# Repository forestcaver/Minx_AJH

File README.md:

# Minx_AJH

Buffered multiple based on Mutable Instruments Links

v1.1 normals the first input jack to ground (if you have v1.0 boards - it's trivial to just jumper the jack !)

BOM spreadsheet is untested - I havent built from this BOM ! Pls check carefully if you use it.

Please note - pcbs and panels are being sold by other people - I have no connection, financial or otherwise, to anyone selling pcbs and panels, hence I feel no commercial obligation to offer build support! I am just freely offering up these designs! Enjoy!

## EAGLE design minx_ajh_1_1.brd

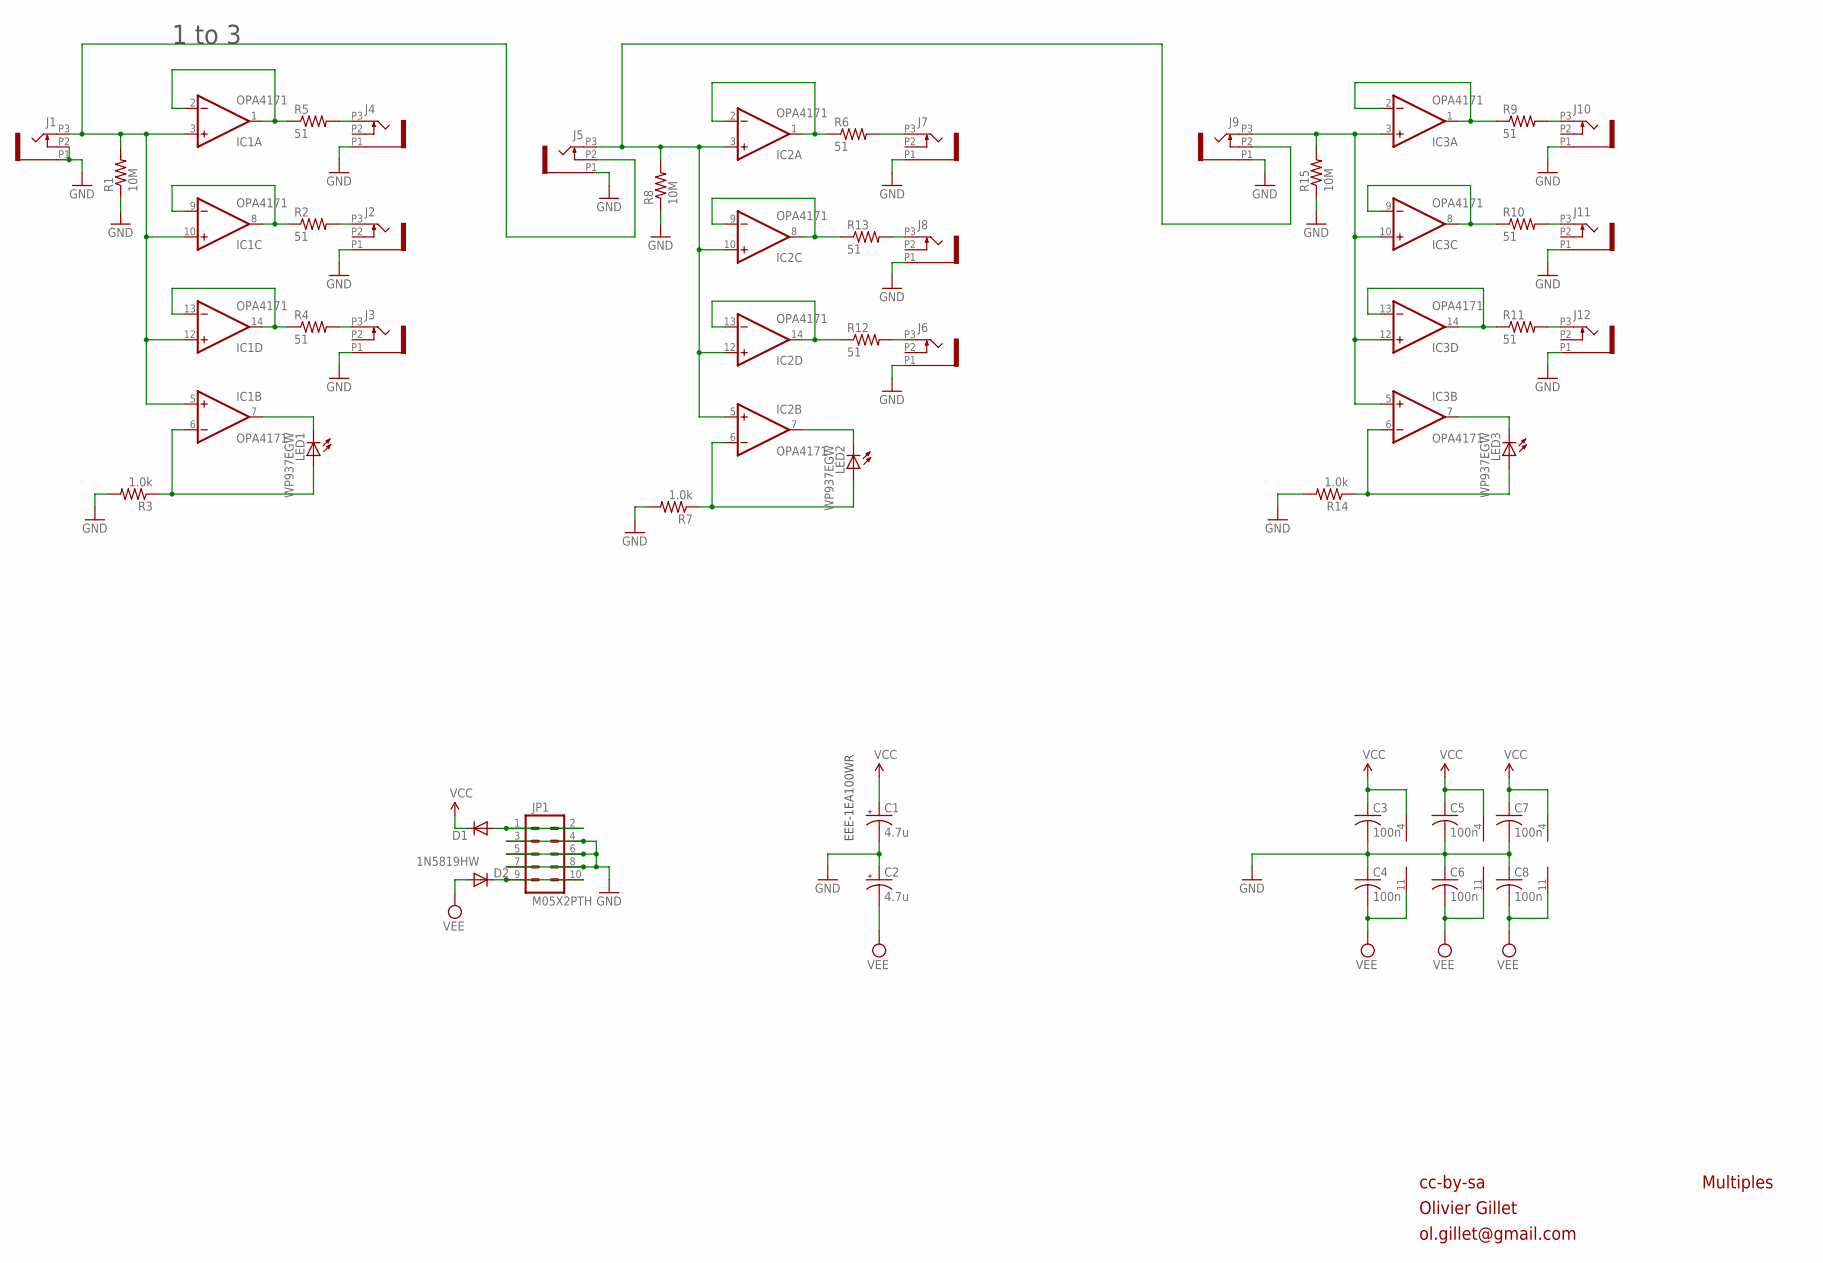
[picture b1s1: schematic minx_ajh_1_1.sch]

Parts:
C1, C2: 4.7u; PANASONIC_A
C3, C4, C5, C6, C7, C8: 100n; C0603
D1, D2: 1N5819HW; SOD123
IC1, IC2, IC3: OPA4171; TSSOP14
J1, J2, J3, J4, J5, J6, J7, J8, J9, J10, J11, J12: PJ301_THONKICONN6; WQP_PJ_301M6
JP1: M05X2PTH; AVR_ICSP
LED1, LED2, LED3: WP937EGW; LED3MM
R1, R8, R15: 10M; R0603
R2, R4, R5, R6, R9, R10, R11, R12, R13: 51; R0603
R3, R7, R14: 1.0k; R0603

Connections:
GND: C1.-, C2.+, C3.2, C4.1, C5.2, C6.1, C7.2, C8.1, J1.P1 (1), J1.P2 (2), J2.P1 (1), J3.P1 (1), J4.P1 (1), J5.P1 (1), J6.P1 (1), J7.P1 (1), J8.P1 (1), J9.P1 (1), J10.P1 (1), J11.P1 (1), J12.P1 (1), JP1.3, JP1.4, JP1.5, JP1.6, JP1.7, JP1.8, R1.1, R3.2, R7.2, R8.1, R14.2, R15.1
unnamed: IC2.8 (OUT), IC2.9 (-IN), R13.1
unnamed: IC3.1 (OUT), IC3.2 (-IN), R9.1
unnamed: J2.P3 (3), R2.2
unnamed: J3.P3 (3), R4.2
unnamed: IC1.13 (-IN), IC1.14 (OUT), R4.1
unnamed: D1.A, JP1.1, JP1.2
unnamed: IC3.13 (-IN), IC3.14 (OUT), R11.1
unnamed: IC1.7 (OUT), LED1.K (C)
unnamed: J7.P3 (3), R6.2
unnamed: IC2.1 (OUT), IC2.2 (-IN), R6.1
unnamed: J4.P3 (3), R5.2
unnamed: J8.P3 (3), R13.2
unnamed: J6.P3 (3), R12.2
unnamed: IC3.7 (OUT), LED3.K (C)
unnamed: J12.P3 (3), R11.2
unnamed: J11.P3 (3), R10.2
unnamed: IC3.6 (-IN), LED3.A, R14.1
unnamed: IC3.8 (OUT), IC3.9 (-IN), R10.1
unnamed: D2.C, JP1.9, JP1.10
unnamed: IC1.6 (-IN), LED1.A, R3.1
unnamed: IC3.3 (+IN), IC3.5 (+IN), IC3.10 (+IN), IC3.12 (+IN), J9.P3 (3), R15.2
unnamed: J10.P3 (3), R9.2
unnamed: IC1.3 (+IN), IC1.5 (+IN), IC1.10 (+IN), IC1.12 (+IN), J1.P3 (3), J5.P2 (2), R1.2
unnamed: IC2.13 (-IN), IC2.14 (OUT), R12.1
unnamed: IC1.1 (OUT), IC1.2 (-IN), R5.1
unnamed: IC2.7 (OUT), LED2.K (C)
unnamed: IC1.8 (OUT), IC1.9 (-IN), R2.1
unnamed: IC2.3 (+IN), IC2.5 (+IN), IC2.10 (+IN), IC2.12 (+IN), J5.P3 (3), J9.P2 (2), R8.2
unnamed: IC2.6 (-IN), LED2.A, R7.1
VCC: C1.+, C3.1, C5.1, C7.1, D1.C, IC1.4 (V+), IC2.4 (V+), IC3.4 (V+)
VEE: C2.-, C4.2, C6.2, C8.2, D2.A, IC1.11 (V-), IC2.11 (V-), IC3.11 (V-)

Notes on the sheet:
cc-by-sa
Olivier Gillet
ol.gillet@gmail.com
Multiples
1 to 3
EEE-1EA100WR

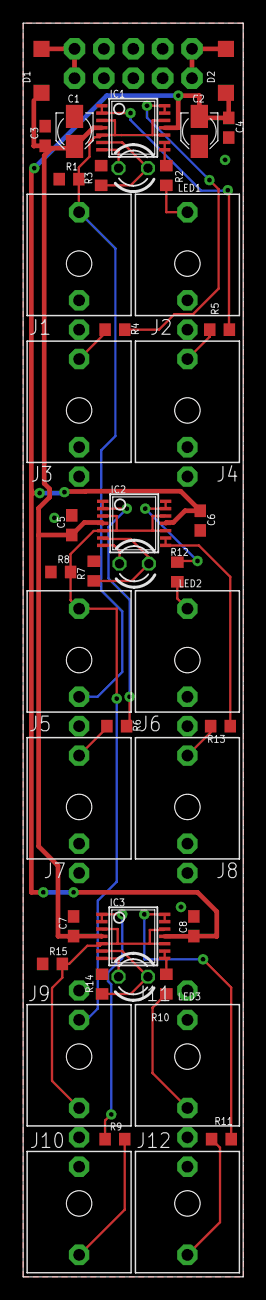
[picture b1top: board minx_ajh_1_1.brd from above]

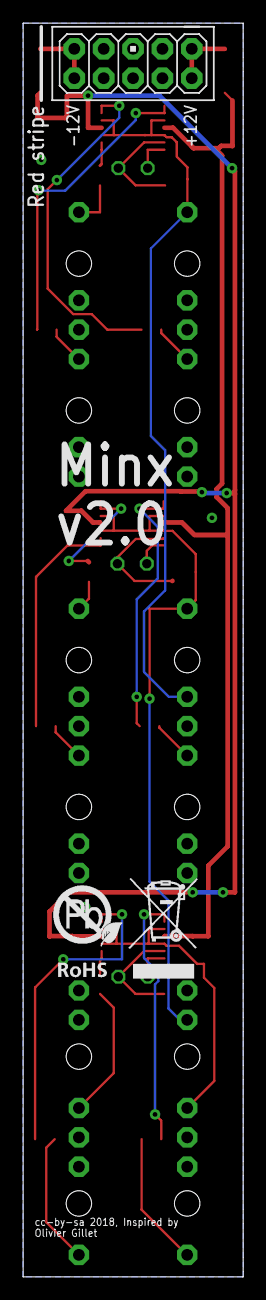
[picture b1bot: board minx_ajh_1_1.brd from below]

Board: 2 copper layers, 19.0 x 108.4 mm, 45 parts (2 on the bottom side), 32 nets.

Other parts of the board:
U$2: ROHS

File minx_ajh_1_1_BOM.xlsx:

minx_ajh_1_1_BOM
Qty | Value | Device | Package | Parts | Description | Ref. Mouser
3 | 1.0k | R-US_R0603 | R0603 | R3, R7, R14 | RESISTOR, American symbol | 667-ERJ3-EKF1001V
6 | 100n | C-USC0603 | C0603 | C3, C4, C5, C6, C7, C8 | CAPACITOR, American symbol | 81-GRM188R71E104JA1J
3 | 10M | R-US_R0603 | R0603 | R1, R8, R15 | RESISTOR, American symbol | 603-RC0603FR-0710ML
2 | 1N5819HW | DIODE-SOD123 | SOD123 | D1, D2 | DIODE | 621-1N5819HW-F
2 | 4.7u | CPOL-USA | PANASONIC_A | C1, C2 | POLARIZED CAPACITOR, American symbol | 647-UWX1E4R7MCL2
9 | 51 | R-US_R0603 | R0603 | R2, R4, R5, R6, R9, R10, R11, R12, R13 | RESISTOR, American symbol | 667-ERJ-3EKF51R0V
1 | M05X2PTH | M05X2PTH | AVR_ICSP | JP1 | Header 5x2 | 649-67996-410HLF
3 | OPA4171 | TL074PW | TSSOP14 | IC1, IC2, IC3 | OP AMP | 595-OPA4171AIPW
12 | PJ301_THONKICONN6 | PJ301_THONKICONN6 | WQP_PJ_301M6 | J1, J2, J3, J4, J5, J6, J7, J8, J9, J10, J11, J12
3 | WP937EGW | LED3MM | LED3MM | LED1, LED2, LED3 | LED | 604-WP937EGW

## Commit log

2020-01-10 Add panel

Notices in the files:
minx_ajh_1_1.brd:
cc-by-sa 2018, Inspired by
Olivier Gillet
